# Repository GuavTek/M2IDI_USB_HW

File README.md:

This eurorack module connects MIDI over USB with the internal MIDI bus, and will work in both USB device and host modes. It also offers stereo audio streaming into and out from the rack when running in device mode. 
View this project on [CADLAB.io](https://cadlab.io/project/25232) to see renders of schematics and PCBs, as well as current issues. 

<h2> A part of the M2IDI prototypes </h2>

<p>
The code for this module can be found on  
<a href="https://github.com/GuavTek/M2IDI_USB">
			  GitHub
		  </a>
</p>

<p> 
More info on the M2IDI system can be found on the 
<a href="https://hackaday.io/project/182092-modular-midi">
			  Hackaday project page
		  </a>

</p>

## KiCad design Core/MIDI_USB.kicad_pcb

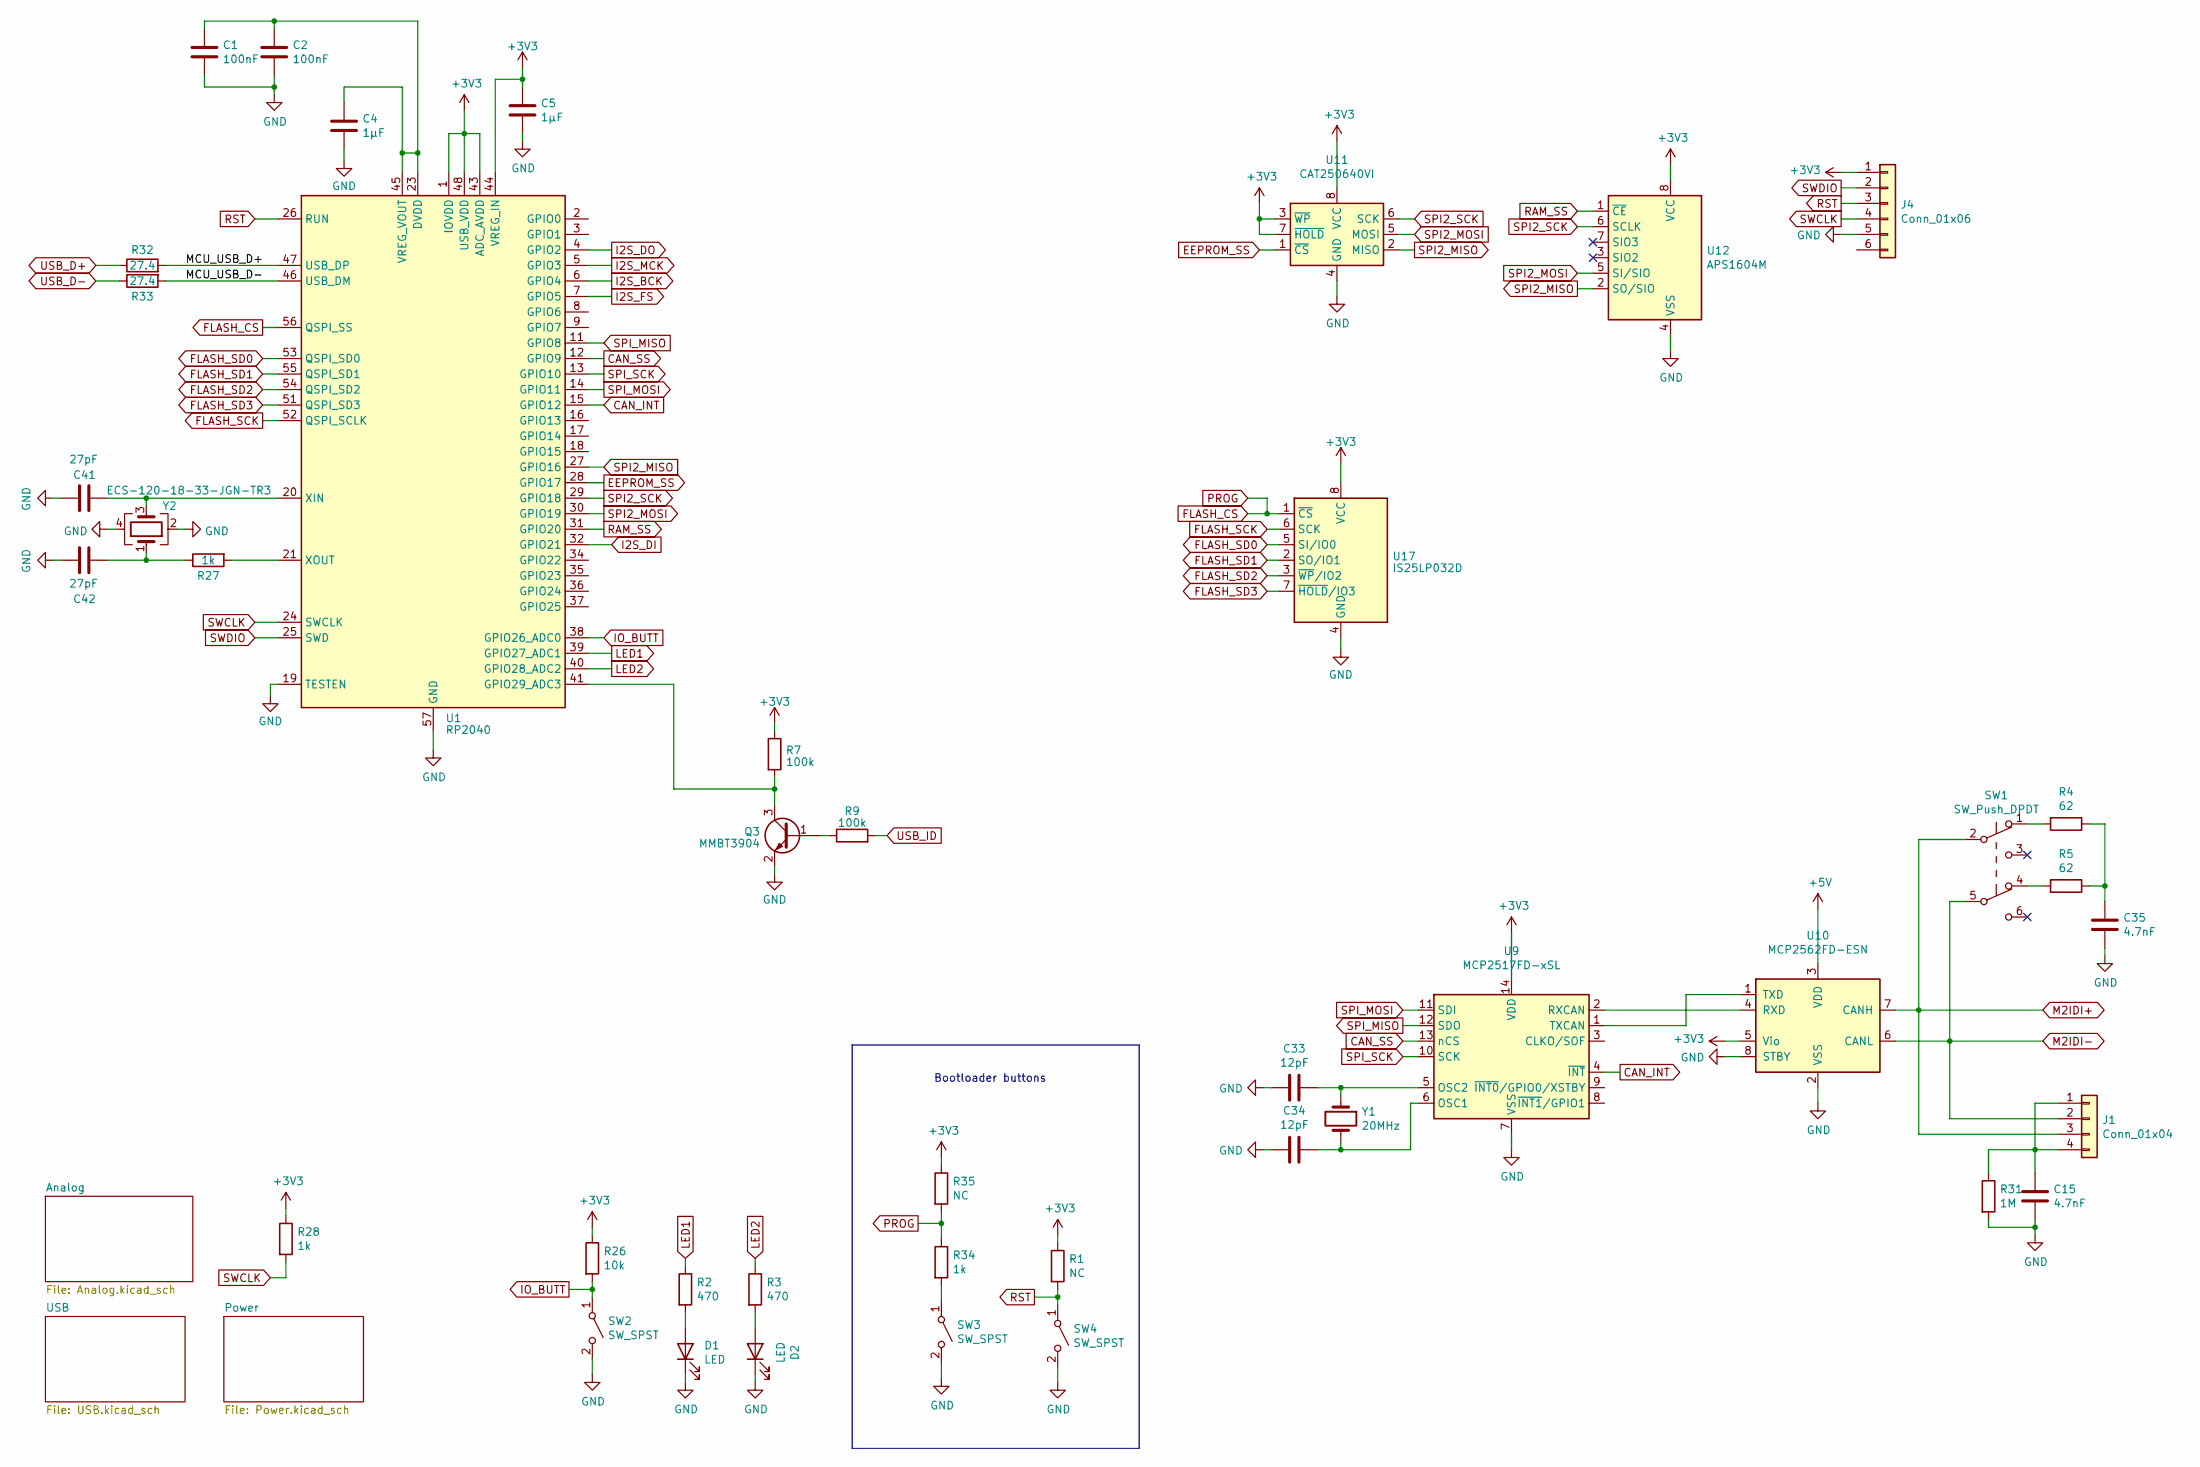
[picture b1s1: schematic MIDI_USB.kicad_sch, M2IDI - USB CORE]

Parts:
C1, C2: 100nF; C_0603_1608Metric
C4, C5: 1µF; C_0603_1608Metric
C15, C35: 4.7nF; C_0603_1608Metric
C33, C34: 12pF; C_0603_1608Metric
C41, C42: 27pF; C_0603_1608Metric
D1: LED; LED_D3.0mm_Horizontal_O1.27mm_Z2.0mm
D2: LED; LED_D3.0mm_Horizontal_O3.81mm_Z2.0mm
J1: Conn_01x04; MicroMatch_04_Angled
J4: Conn_01x06; PinHeader_2x03_P2.54mm_Vertical_SMD
Q3: MMBT3904; SOT-23
R1, R35: NC; R_0603_1608Metric
R2, R3: 470; R_0603_1608Metric
R4, R5: 62; R_0805_2012Metric
R7, R9: 100k; R_0603_1608Metric
R26: 10k; R_0603_1608Metric
R27, R28, R34: 1k; R_0603_1608Metric
R31: 1M; R_0603_1608Metric
R32, R33: 27.4; R_0603_1608Metric
SW1: SW_Push_DPDT; SlideDPDT_JS202011
SW2: SW_SPST; SW_Tactile_SPST_Angled_PTS645Vx58-2LFS
SW3, SW4: SW_SPST; SW_SPST_B3U-1000P
U1: RP2040; QFN-56-1EP_7x7mm_P0.4mm_EP3.2x3.2mm
U9: MCP2517FD-xSL; SOIC-14_3.9x8.7mm_P1.27mm
U10: MCP2562FD-ESN; SOIC-8_3.9x4.9mm_P1.27mm
U11: CAT250640VI; SOIC-8_3.9x4.9mm_P1.27mm
U12: APS1604M; SOIC-8_3.9x4.9mm_P1.27mm
U17: IS25LP032D; SOIC-8_3.9x4.9mm_P1.27mm
Y1: 20MHz; Crystal_2pin_2.0x2.5mm
Y2: ECS-120-18-33-JGN-TR3; Crystal_SMD_3225-4Pin_3.2x2.5mm_HandSoldering

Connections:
+3V3: C5.1, J4.1, R1.1, R7.1, R26.1, R28.1, R35.1, U1.1 (IOVDD), U1.10 (IOVDD), U1.22 (IOVDD), U1.33 (IOVDD), U1.42 (IOVDD), U1.43 (ADC_AVDD), U1.44 (VREG_IN), U1.48 (USB_VDD), U1.49 (IOVDD), U9.14 (VDD), U10.5 (Vio), U11.3 (~WP), U11.7 (~HOLD), U11.8 (VCC), U12.8 (VCC); also elsewhere on the board
/MCU_USB_D+: R32.2, U1.47 (USB_DP); also elsewhere on the board
/MCU_USB_D-: R33.2, U1.46 (USB_DM)
CAN_INT: U1.15 (GPIO12), U9.4 (~INT)
CAN_SS: U1.12 (GPIO9), U9.13 (nCS)
EEPROM_SS: U1.28 (GPIO17), U11.1 (~CS)
FLASH_CS: R34.1, R35.2, U1.56 (QSPI_SS); also elsewhere on the board
FLASH_SCK: U1.52 (QSPI_SCLK); also elsewhere on the board
FLASH_SD0: U1.53 (QSPI_SD0); also elsewhere on the board
FLASH_SD1: U1.55 (QSPI_SD1); also elsewhere on the board
FLASH_SD2: U1.54 (QSPI_SD2); also elsewhere on the board
FLASH_SD3: U1.51 (QSPI_SD3); also elsewhere on the board
I2S_BCK: U1.6 (GPIO4); also elsewhere on the board
I2S_DI: U1.32 (GPIO21); also elsewhere on the board
I2S_DO: U1.4 (GPIO2); also elsewhere on the board
I2S_FS: U1.7 (GPIO5); also elsewhere on the board
I2S_MCK: U1.5 (GPIO3); also elsewhere on the board
IO_BUTT: R26.2, SW2.1 (A), U1.38 (GPIO26_ADC0)
LED1: R2.1, U1.39 (GPIO27_ADC1)
LED2: R3.1, U1.40 (GPIO28_ADC2)
M2IDI+: J1.3, SW1.2 (B), U10.7 (CANH)
M2IDI-: J1.2, SW1.5 (B), U10.6 (CANL)
unnamed: C35.1, R4.1, R5.1
unnamed: C42.1, R27.1, Y2.1
unnamed: D1.2 (A), R2.2
unnamed: D2.2 (A), R3.2
unnamed: C15.1, J1.1, J1.4, R31.1
unnamed: Q3.1 (B), R9.1
unnamed: Q3.3 (C), R7.2, U1.41 (GPIO29_ADC3)
unnamed: R4.2, SW1.1 (A)
unnamed: R5.2, SW1.4 (A)
unnamed: R34.2, SW3.1 (A)
unnamed: C1.1, C2.1, C4.1, U1.23 (DVDD), U1.45 (VREG_VOUT), U1.50 (DVDD)
unnamed: C41.1, U1.20 (XIN), Y2.3
unnamed: R27.2, U1.21 (XOUT)
unnamed: C34.1, U9.6 (OSC1), Y1.2
unnamed: C33.1, U9.5 (OSC2), Y1.1
unnamed: U9.2 (RXCAN), U10.4 (RXD)
unnamed: U9.1 (TXCAN), U10.1 (TXD)
RAM_SS: U1.31 (GPIO20), U12.1 (~CE)
RST: J4.3, R1.2, SW4.1 (A), U1.26 (RUN)
SPI2_MISO: U1.27 (GPIO16), U11.2 (MISO), U12.2 (SO/SIO)
SPI2_MOSI: U1.30 (GPIO19), U11.5 (MOSI), U12.5 (SI/SIO)
SPI2_SCK: U1.29 (GPIO18), U11.6 (SCK), U12.6 (SCLK)
SPI_MISO: U1.11 (GPIO8), U9.12 (SDO)
SPI_MOSI: U1.14 (GPIO11), U9.11 (SDI)
SPI_SCK: U1.13 (GPIO10), U9.10 (SCK)
SWCLK: J4.4, R28.2, U1.24 (SWCLK)
SWDIO: J4.2, U1.25 (SWD)
USB_D-: R33.1; also elsewhere on the board

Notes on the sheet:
Bootloader buttons

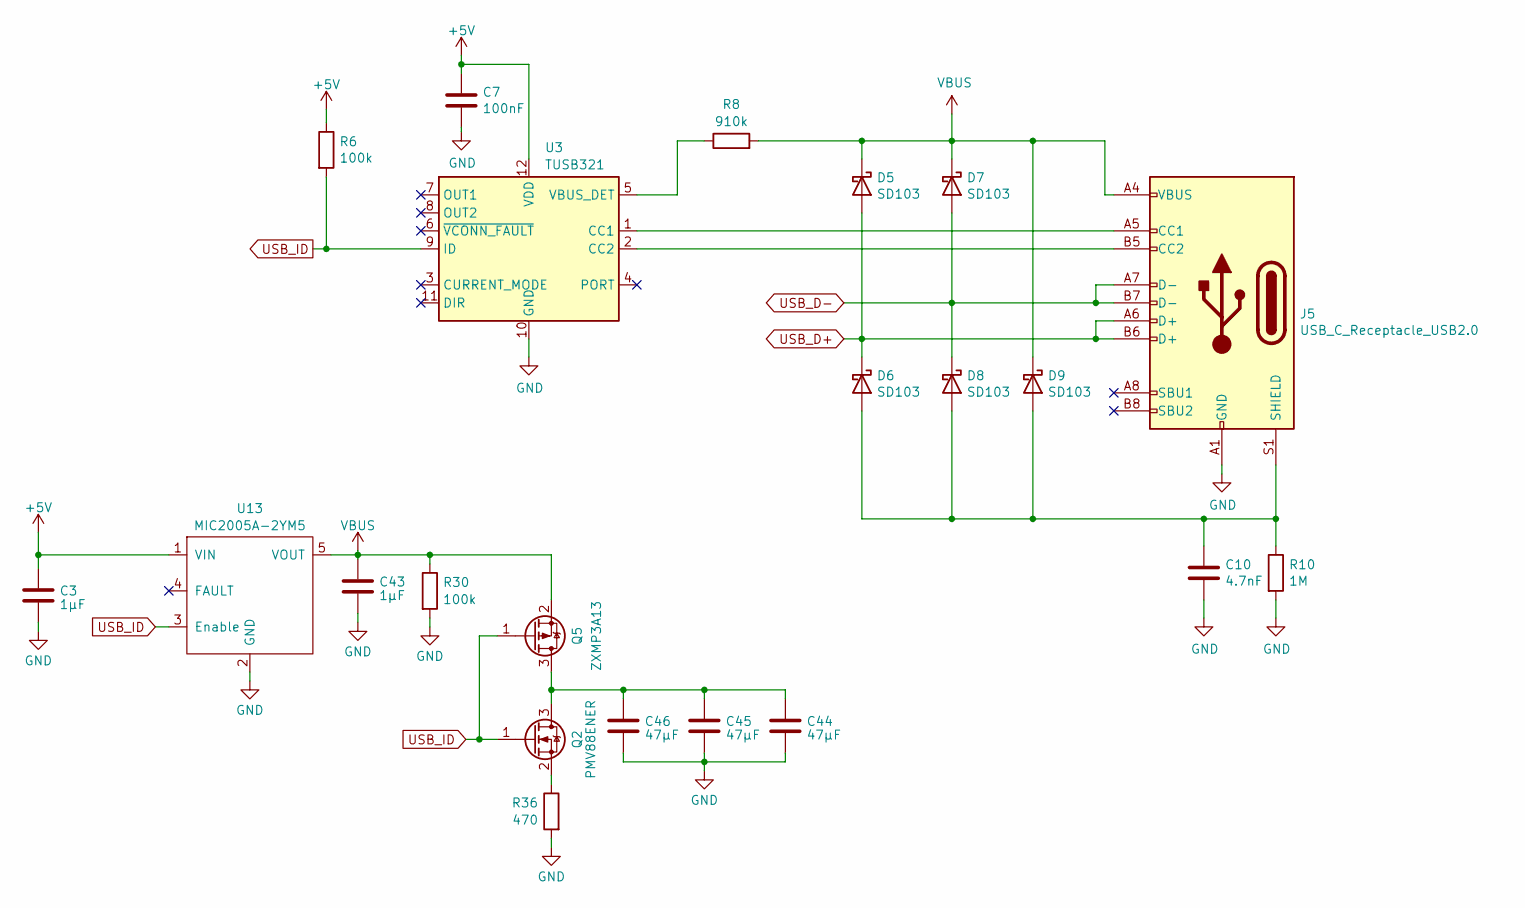
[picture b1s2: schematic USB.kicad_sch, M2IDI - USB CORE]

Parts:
C3, C43: 1µF; C_0603_1608Metric
C7: 100nF; C_0603_1608Metric
C10: 4.7nF; C_0603_1608Metric
C44, C45, C46: 47µF; C_1210_3225Metric
D5, D6, D7, D8, D9: SD103; D_SOD-323_HandSoldering
J5: USB_C_Receptacle_USB2.0; USB_C_Receptacle_HRO_TYPE-C-31-M-12
Q2: PMV88ENER; SOT-23
Q5: ZXMP3A13; SOT-23
R6, R30: 100k; R_0603_1608Metric
R8: 910k; R_0603_1608Metric
R10: 1M; R_0603_1608Metric
R36: 470; R_0603_1608Metric
U3: TUSB321; Texas_X2QFN-12_1.6x1.6mm_P0.4mm
U13: MIC2005A-2YM5; SOT-23-5

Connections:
unnamed: C10.1, D6.2 (A), D8.2 (A), D9.2 (A), J5.S1 (SHIELD), R10.1
unnamed: J5.A5 (CC1), U3.1 (CC1)
unnamed: J5.B5 (CC2), U3.2 (CC2)
unnamed: R8.1, U3.5 (VBUS_DET)
USB_D+: D5.2 (A), D6.1 (K), J5.A6 (D+), J5.B6 (D+); also elsewhere on the board
USB_D-: D7.2 (A), D8.1 (K), J5.A7 (D-), J5.B7 (D-); also elsewhere on the board

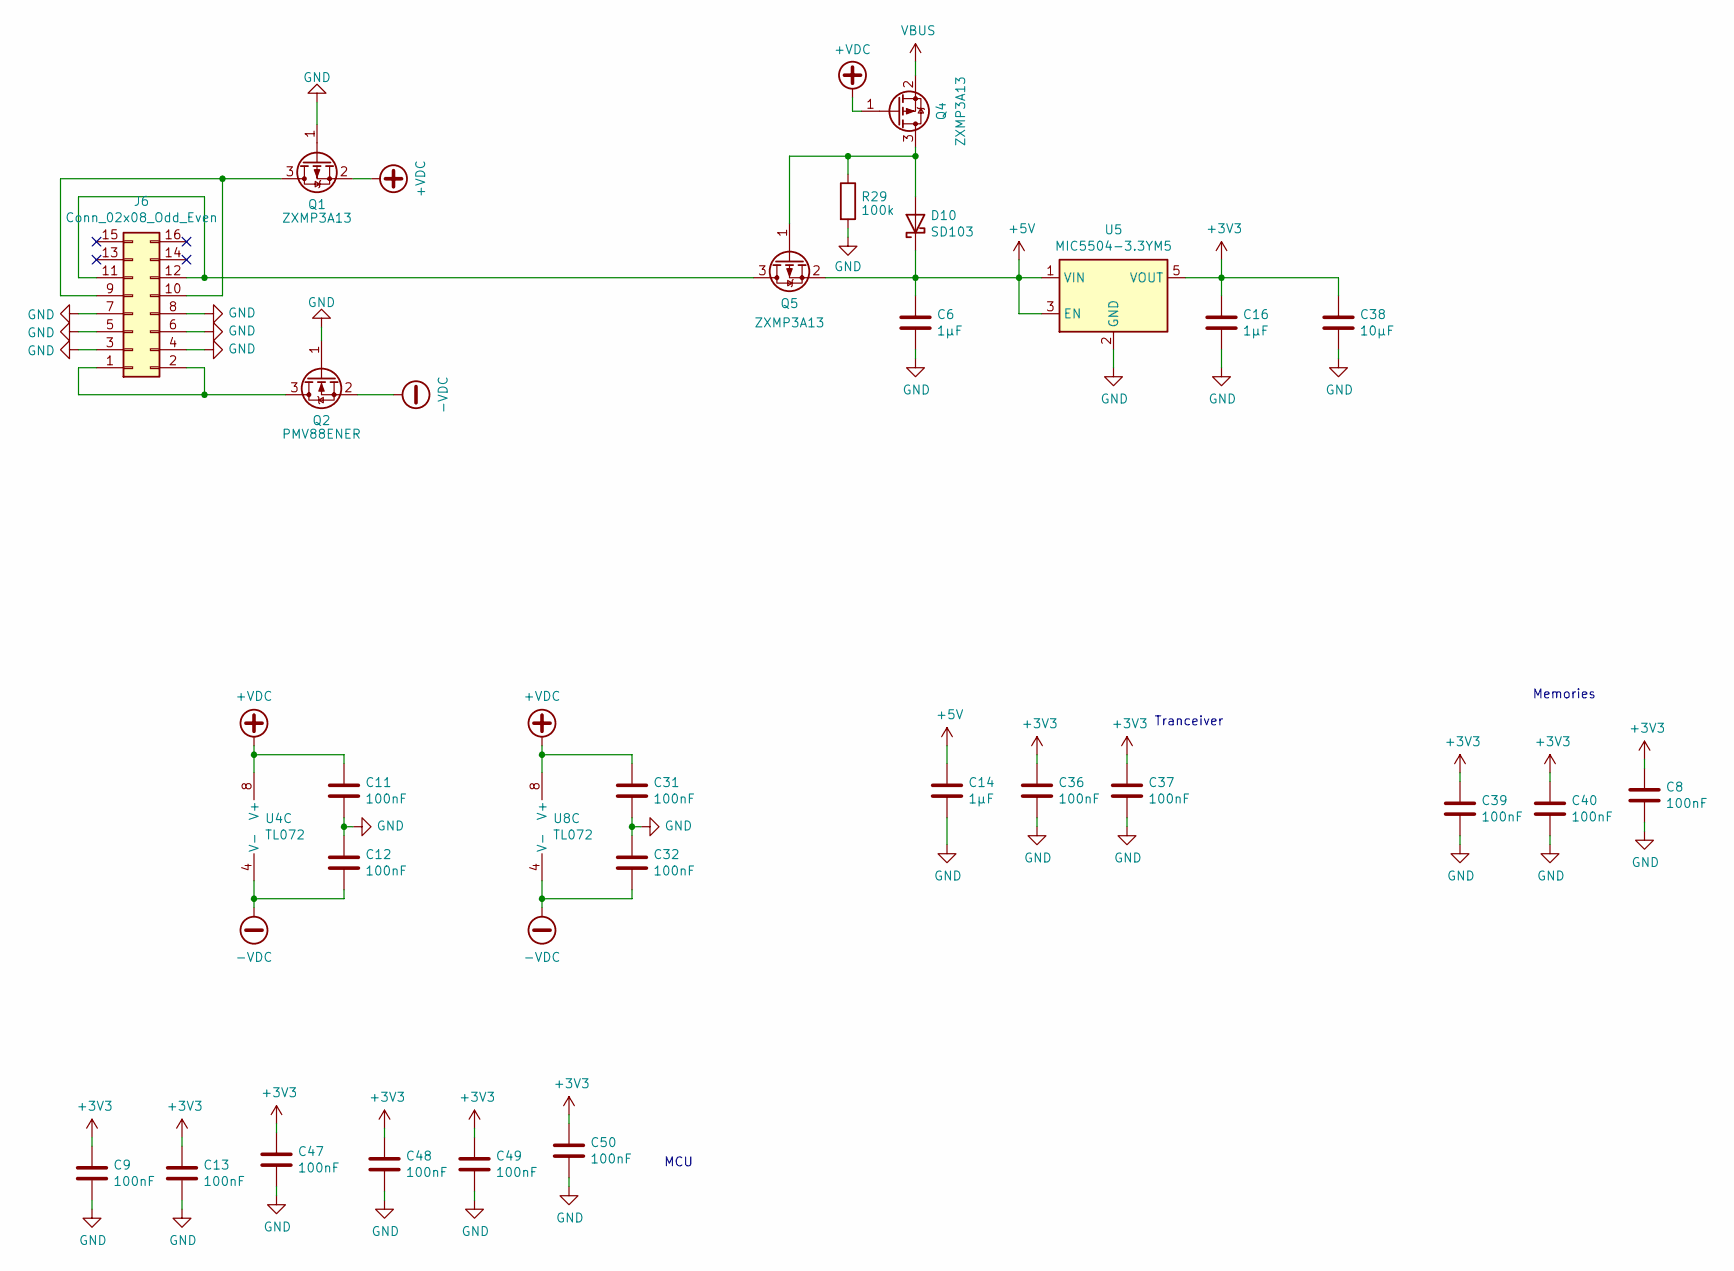
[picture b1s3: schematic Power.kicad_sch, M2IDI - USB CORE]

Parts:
C6, C14, C16: 1µF; C_0603_1608Metric
C8, C9, C11, C12, C13, C31, C32, C36, C37, C39, C40, C47, C48, C49, C50: 100nF; C_0603_1608Metric
C38: 10µF; C_0805_2012Metric
D10: SD103; D_SOD-323_HandSoldering
J6: Conn_02x08_Odd_Even; PinHeader_2x08_P2.54mm_Horizontal
Q1, Q4, Q5: ZXMP3A13; SOT-23
Q2: PMV88ENER; SOT-23
R29: 100k; R_0603_1608Metric
U4, U8: TL072; SO-8_3.9x4.9mm_P1.27mm
U5: MIC5504-3.3YM5; SOT-23-5

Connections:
+3V3: C8.1, C9.1, C13.1, C16.1, C36.1, C37.1, C38.1, C39.1, C40.1, C47.1, C48.1, C49.1, C50.1, U5.5 (VOUT); also elsewhere on the board
+VDC: C11.1, C31.1, Q1.2 (S), Q4.1 (G), U4.8 (V+), U8.8 (V+)
unnamed: J6.9, J6.10, Q1.3 (D)

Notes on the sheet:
Tranceiver
Memories
MCU

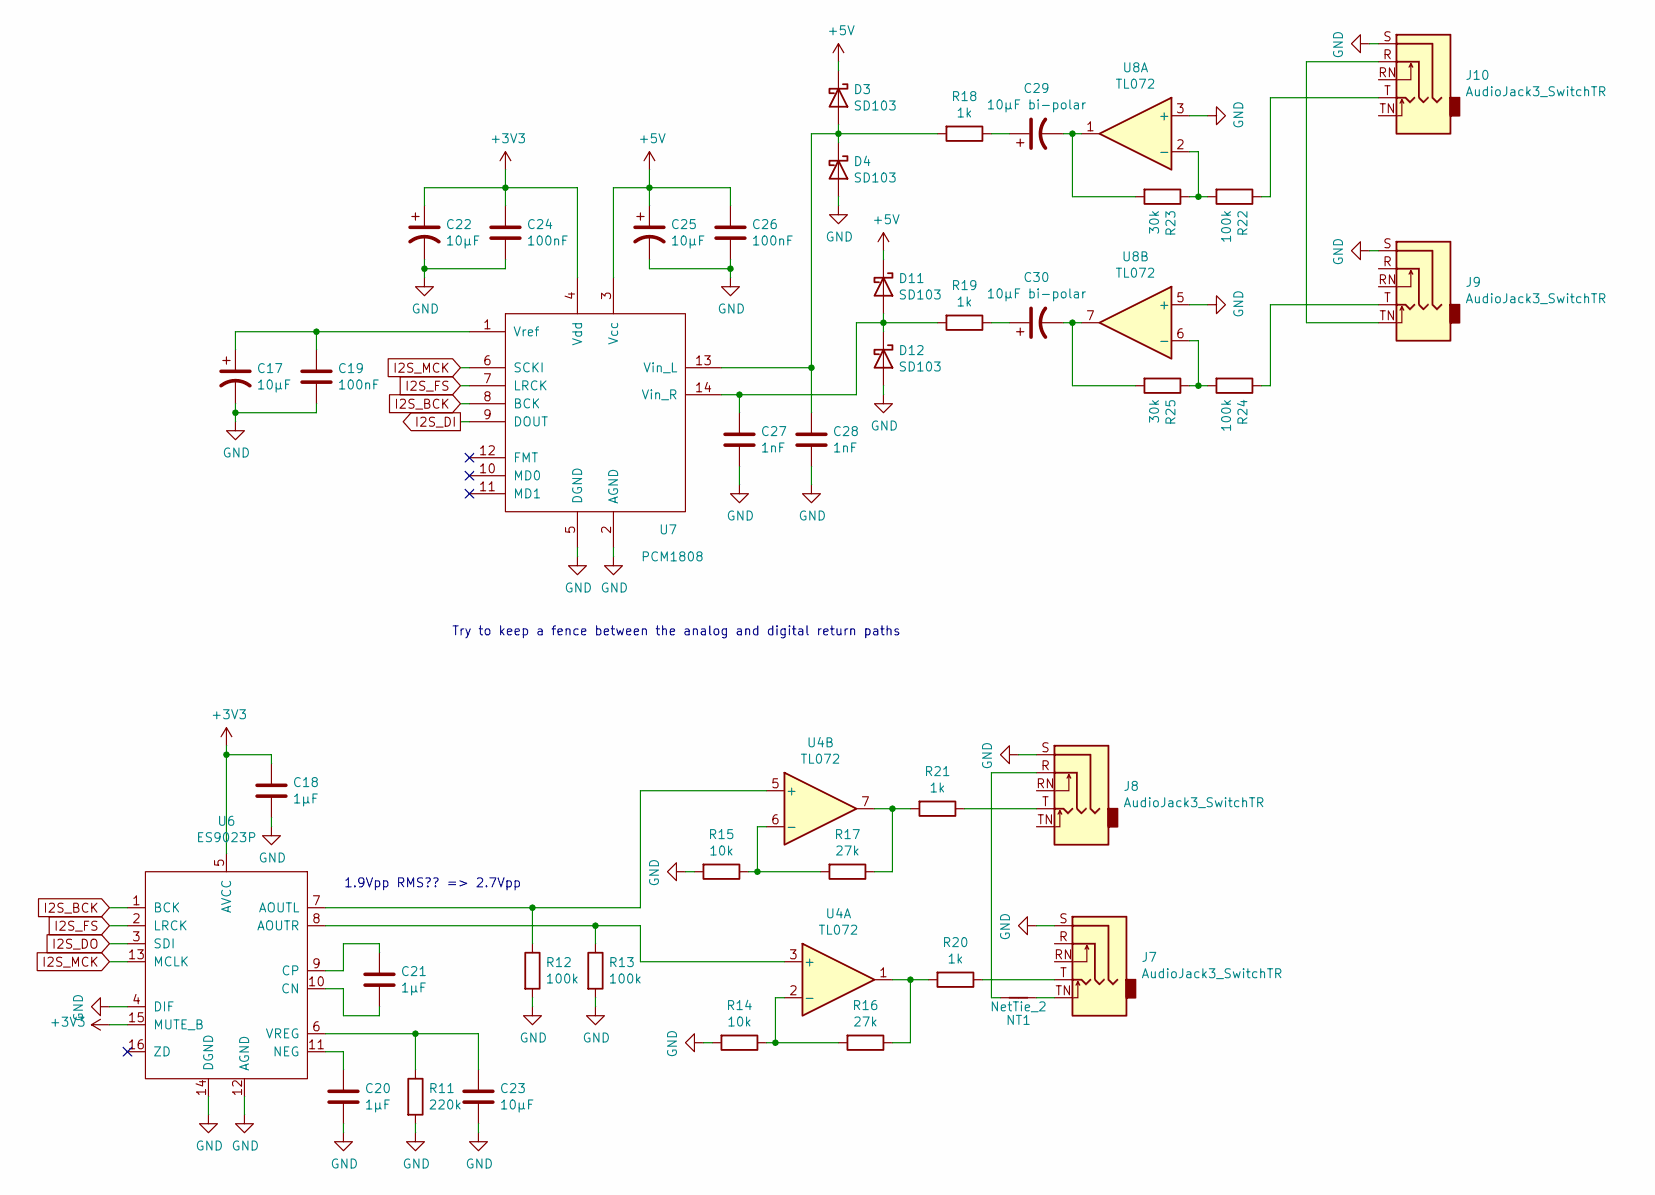
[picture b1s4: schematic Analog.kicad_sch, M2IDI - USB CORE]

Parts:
C17, C22, C23, C25: 10µF; C_0805_2012Metric
C18, C20, C21: 1µF; C_0603_1608Metric
C19, C24, C26: 100nF; C_0603_1608Metric
C27, C28: 1nF; C_0603_1608Metric
C29, C30: 10µF bi-polar; CP_Elec_5x5.8
D3, D4, D11, D12: SD103; D_SOD-323_HandSoldering
J7, J8, J9, J10: AudioJack3_SwitchTR; STX3100_Angled_3.5mm
NT1: NetTie_2; SolderJumper-2_P1.3mm_Open_RoundedPad1.0x1.5mm
R11: 220k; R_0603_1608Metric
R12, R13, R22, R24: 100k; R_0603_1608Metric
R14, R15: 10k; R_0603_1608Metric
R16, R17: 27k; R_0603_1608Metric
R18, R19, R20, R21: 1k; R_0603_1608Metric
R23, R25: 30k; R_0603_1608Metric
U4, U8: TL072; SO-8_3.9x4.9mm_P1.27mm
U6: ES9023P; SOIC-16_3.9x9.9mm_P1.27mm
U7: PCM1808; TSSOP-14_4.4x5mm_P0.65mm

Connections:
+3V3: C18.1, C22.1, C24.1, U6.5 (AVCC), U6.15 (MUTE_B), U7.4 (Vdd); also elsewhere on the board
I2S_BCK: U6.1 (BCK), U7.8 (BCK); also elsewhere on the board
I2S_DI: U7.9 (DOUT); also elsewhere on the board
I2S_DO: U6.3 (SDI); also elsewhere on the board
I2S_FS: U6.2 (LRCK), U7.7 (LRCK); also elsewhere on the board
I2S_MCK: U6.13 (MCLK), U7.6 (SCKI); also elsewhere on the board
unnamed: C29.1, R18.1
unnamed: C29.2, R23.2, U8.1
unnamed: C30.1, R19.1
unnamed: C30.2, R25.2, U8.7
unnamed: C28.1, D3.2 (A), D4.1 (K), R18.2, U7.13 (Vin_L)
unnamed: C27.1, D11.2 (A), D12.1 (K), R19.2, U7.14 (Vin_R)
unnamed: J7.T, R20.1
unnamed: J7.TN, NT1.1
unnamed: J8.R, NT1.2
unnamed: J8.T, R21.1
unnamed: J9.T, R24.1
unnamed: J9.TN, J10.R
unnamed: J10.T, R22.1
unnamed: R16.1, R20.2, U4.1
unnamed: R17.1, R21.2, U4.7
unnamed: R13.1, U4.3 (+), U6.8 (AOUTR)
unnamed: R14.1, R16.2, U4.2 (-)
unnamed: R12.1, U4.5 (+), U6.7 (AOUTL)
unnamed: R15.1, R17.2, U4.6 (-)
unnamed: C21.2, U6.10 (CN)
unnamed: C21.1, U6.9 (CP)
unnamed: C20.1, U6.11 (NEG)
unnamed: C23.1, R11.1, U6.6 (VREG)
unnamed: C17.1, C19.1, U7.1 (Vref)
unnamed: R22.2, R23.1, U8.2 (-)
unnamed: R24.2, R25.1, U8.6 (-)

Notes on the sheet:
1.9Vpp RMS?? => 2.7Vpp
Try to keep a fence between the analog and digital return paths

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
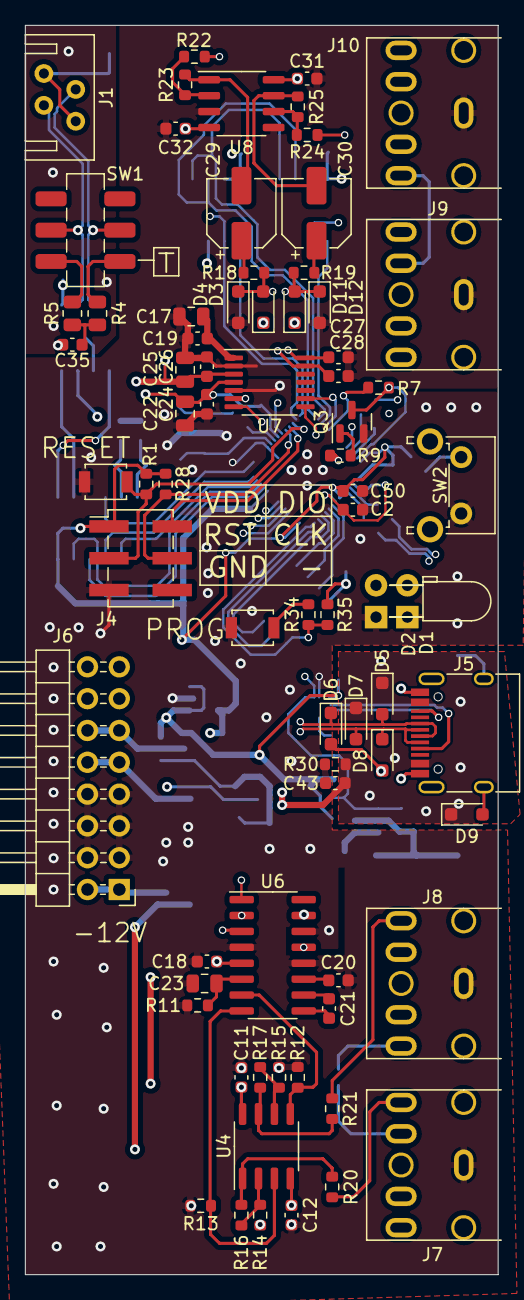
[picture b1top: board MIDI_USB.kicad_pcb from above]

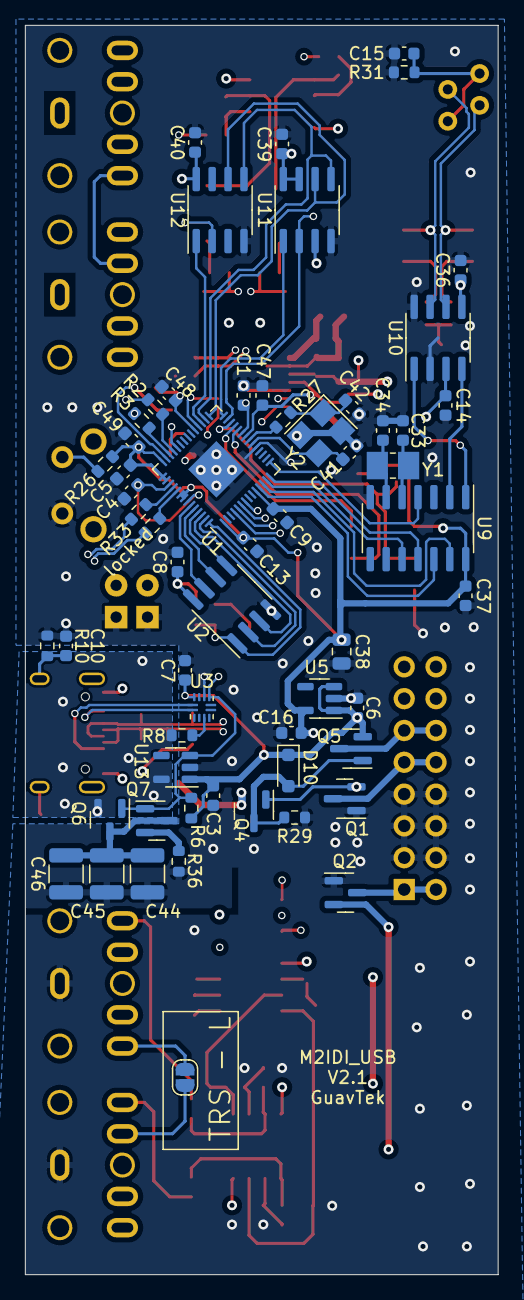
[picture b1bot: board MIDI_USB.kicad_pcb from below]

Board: 4 copper layers, 37.8 x 99.8 mm, 133 parts (59 on the bottom side), 93 nets.

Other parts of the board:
Q6: ZXMP3A13; SOT-23
Q7: PMV88ENER; SOT-23
U2: IS25LP032D; SOIC-8_3.9x4.9mm_P1.27mm
locked: 27.4; R_0603_1608Metric

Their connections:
+3V3: U2.8 (VCC); also elsewhere on the board
/MCU_USB_D+: locked.2; also elsewhere on the board
FLASH_CS: U2.1 (~CS); also elsewhere on the board
FLASH_SCK: U2.6 (SCK); also elsewhere on the board
FLASH_SD0: U2.5 (SI/IO0); also elsewhere on the board
FLASH_SD1: U2.2 (SO/IO1); also elsewhere on the board
FLASH_SD2: U2.3 (~WP/IO2); also elsewhere on the board
FLASH_SD3: U2.7 (~HOLD/IO3); also elsewhere on the board
USB_D+: locked.1; also elsewhere on the board

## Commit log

2021-10-27 Add all the files
2021-10-27 Update AutoGerber.yml
    Maybe fix file paths
2021-10-27 Update filenames
2021-10-27 Fix DRC
2022-02-17 Adjust filenames
2022-02-17 Backlink to CADLAB.io has been added.
2022-02-18 Fix symbols
2022-02-18 Include symbol library
2022-02-18 Fix library path
2022-02-19 Add custom footprints
2022-02-19 Fix part number
2022-06-30 Reduce distortion in ADC circuit
2022-06-30 Change to SMD USB connector
2022-06-30 Add external EEPROM and RAM
2022-06-30 Add IO and bootloader buttons
2022-07-02 Fix DAC amplitude
2022-07-02 Add external RTC oscillator
2023-04-08 Update front panel
2023-05-10 Fix action version
2023-06-11 Update front panel layout
2023-06-11 Minor fixes
2023-06-13 Adjust vias
2023-06-18 Switch to RP2040
2023-06-18 Update metadata
2023-06-19 Add optional solder bridge++
2023-07-09 Change CAN tranceiver to MCP2562
2023-07-09 Fix crystal footprint
2023-07-12 Re-arrange USB components
2023-07-14 Adjust 5V power protection
2023-09-01 Finalize module
2023-09-10 Remove old kicad files
2023-09-17 Increase button hole size
2023-09-17 Re-add Custom_FP library
2024-01-27 Change USB id chips to TUSB321 and MID2005
2024-03-31 Switch from CC license to CERN open hardware
